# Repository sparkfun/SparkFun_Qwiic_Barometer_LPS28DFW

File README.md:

# SparkFun_Qwiic_Barometer_LPS28DFW

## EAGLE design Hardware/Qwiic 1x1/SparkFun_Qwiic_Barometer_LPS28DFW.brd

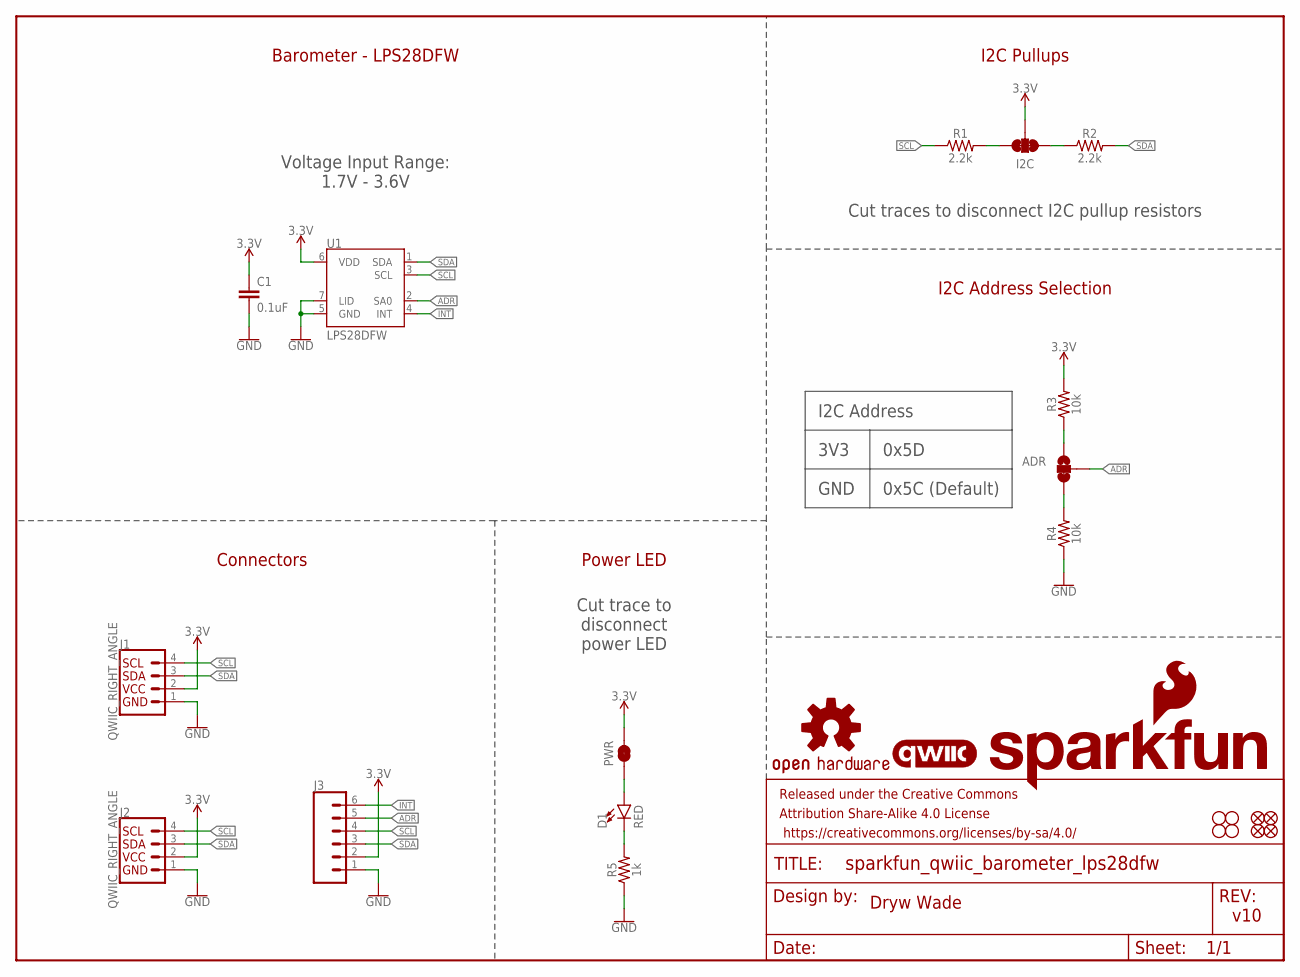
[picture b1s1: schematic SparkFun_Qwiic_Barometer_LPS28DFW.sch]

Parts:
ADR: JUMPER-SMT_3_1-NC_TRACE_SILK; SMT-JUMPER_3_1-NC_TRACE_SILK
C1: 0.1uF; 0603
D1: RED; LED-0603
FD1, FD2, FD3, FD4: FIDUCIAL1X2; FIDUCIAL-1X2
FRAME1: FRAME-LETTER; CREATIVE_COMMONS
H1, H2, H3, H4: STAND-OFF
I2C: JUMPER-SMT_3_2-NC_TRACE_SILK; SMT-JUMPER_3_2-NC_TRACE_SILK
J1, J2: QWIIC_RIGHT_ANGLE; JST04_1MM_RA
J3: CONN_06NO_SILK_NO_POP; 1X06_NO_SILK
LOGO1: OSHW-LOGOS; OSHW-LOGO-S
LOGO2: QWIIC_LOGO_5MM; QWIIC_5MM
LOGO3: SFE_LOGO_NAME_FLAME.1_INCH; SFE_LOGO_NAME_FLAME_.1
PWR: JUMPER-SMT_2_NC_TRACE_SILK; SMT-JUMPER_2_NC_TRACE_SILK
R1, R2: 2.2k; 0603
R3, R4: 10k; 0603
R5: 1k; 0603
U1: LPS28DFW

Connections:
3.3V: C1.1, I2C.2, J1.2, J2.2, J3.2, PWR.2, R3.2, U1.6 (VDD)
ADR: ADR.2, J3.5, U1.2 (SA0)
GND: C1.2, J1.1, J2.1, J3.1, R4.1, R5.1, U1.5 (GND), U1.7 (LID)
INT: J3.6, U1.4 (INT)
unnamed: D1.C, R5.2
unnamed: I2C.3, R1.2
unnamed: I2C.1, R2.1
unnamed: D1.A, PWR.1
unnamed: ADR.3, R4.2
unnamed: ADR.1, R3.1
SCL: J1.4, J2.4, J3.4, R1.1, U1.3 (SCL)
SDA: J1.3, J2.3, J3.3, R2.2, U1.1 (SDA)

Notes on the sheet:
Dryw Wade
v10
Barometer - LPS28DFW
I2C Pullups
I2C Address Selection
Connectors
Power LED
Cut traces to disconnect I2C pullup resistors
I2C Address
GND
3V3
0x5D
0x5C (Default)
Cut trace to disconnect power LED
Voltage Input Range: 1.7V - 3.6V

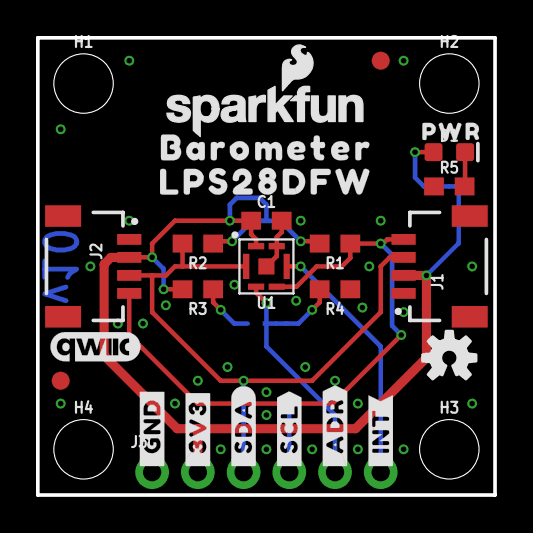
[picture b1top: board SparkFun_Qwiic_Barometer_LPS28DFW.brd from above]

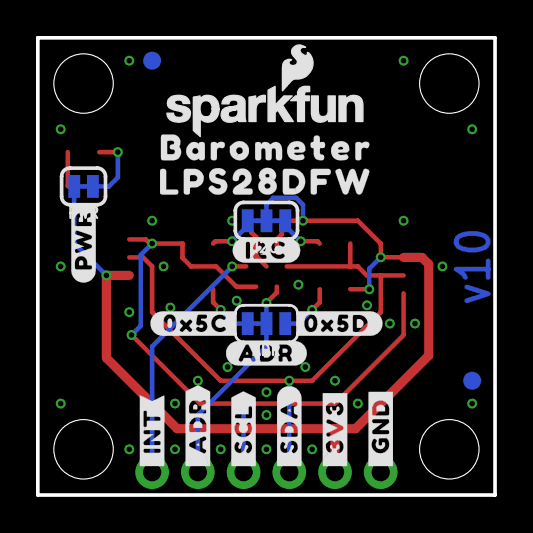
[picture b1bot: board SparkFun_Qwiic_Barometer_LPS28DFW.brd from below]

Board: 2 copper layers, 25.4 x 25.4 mm, 50 parts (19 on the bottom side), 12 nets.

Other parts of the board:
LOGO4: SFE_LOGO_NAME_FLAME.1_INCH; SFE_LOGO_NAME_FLAME_.1
U$1, U$2: #_GND#0
U$3, U$4: #_3V3#0
U$5, U$6: #_SDA#0
U$7, U$8: #_SCL#0
U$9: #I2C#0
U$10: #ADR#0
U$11, U$14: BAROMETER0
U$12, U$15: LPS28DFW0
U$13: #PWR#0
U$16: #0X5D#0
U$17: #0X5C#0
U$18: PWR0
U$19: ORDERING_INSTRUCTIONS
U$20, U$21: #_INT#0
U$22, U$23: #_ADR#0

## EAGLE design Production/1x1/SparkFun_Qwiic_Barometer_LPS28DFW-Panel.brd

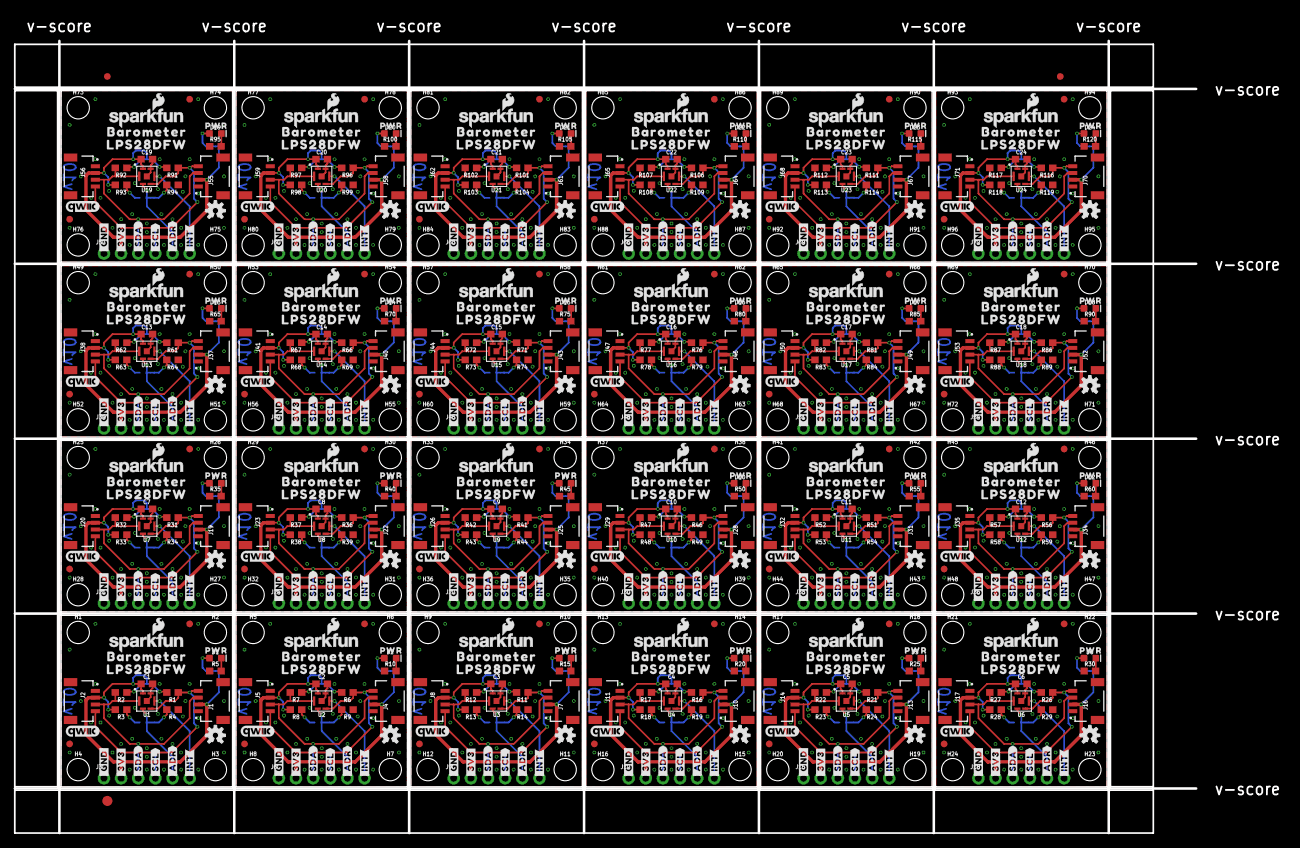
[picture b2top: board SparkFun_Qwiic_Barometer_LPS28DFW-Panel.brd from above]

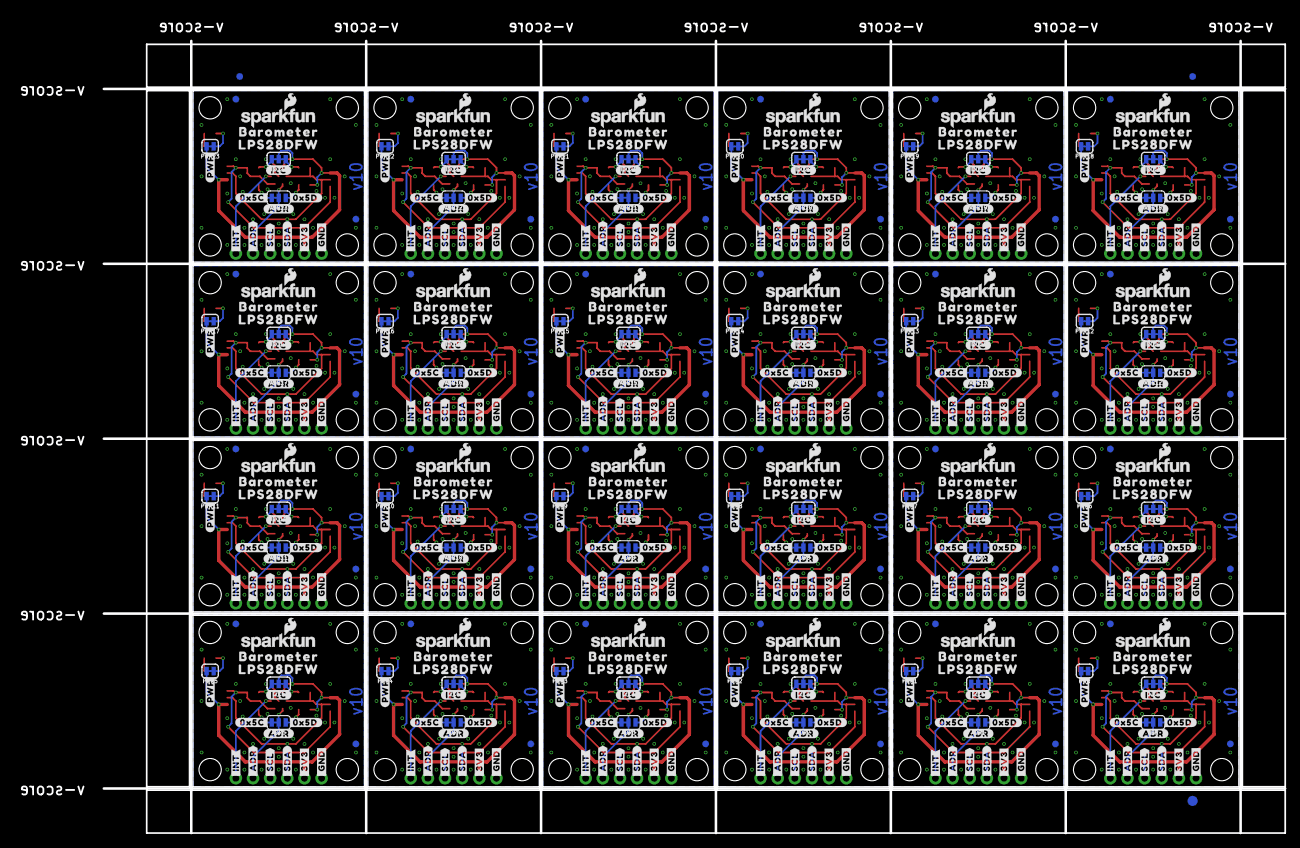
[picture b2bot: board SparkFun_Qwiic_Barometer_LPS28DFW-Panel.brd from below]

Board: 2 copper layers, 188.2 x 121.2 mm, 1158 parts (459 on the bottom side), 288 nets.

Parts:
ADR, ADR1, ADR2, ADR3, ADR4, ADR5, ADR6, ADR7, ADR8, ADR9, ADR10, ADR11, ADR12, ADR13, ADR14, ADR15, ADR16, ADR17, ADR18, ADR19, ADR20, ADR21, ADR22, ADR23: JUMPER-SMT_3_1-NC_TRACE_SILK; SMT-JUMPER_3_1-NC_TRACE_SILK
C1, C2, C3, C4, C5, C6, C7, C8, C9, C10, C11, C12, C13, C14, C15, C16, C17, C18, C19, C20, C21, C22, C23, C24: 0.1uF; 0603
D1, D2, D3, D4, D5, D6, D7, D8, D9, D10, D11, D12, D13, D14, D15, D16, D17, D18, D19, D20, D21, D22, D23, D24: RED; LED-0603
E$1, E$2, E$3, E$4: FIDUCIAL-1X2
E$5, E$6: FIDUCIAL-1.5X3
FD1, FD2, FD3, FD4, FD5, FD6, FD7, FD8, FD9, FD10, FD11, FD12, FD13, FD14, FD15, FD16, FD17, FD18, FD19, FD20, FD21, FD22, FD23, FD24, FD25, FD26, FD27, FD28, FD29, FD30, FD31, FD32, FD33, FD34, FD35, FD36, FD37, FD38, FD39, FD40, FD41, FD42, FD43, FD44, FD45, FD46, FD47, FD48, FD49, FD50, FD51, FD52, FD53, FD54, FD55, FD56, FD57, FD58, FD59, FD60, FD61, FD62, FD63, FD64, FD65, FD66, FD67, FD68, FD69, FD70, FD71, FD72, FD73, FD74, FD75, FD76, FD77, FD78, FD79, FD80, FD81, FD82, FD83, FD84, FD85, FD86, FD87, FD88, FD89, FD90, FD91, FD92, FD93, FD94, FD95, FD96: FIDUCIAL1X2; FIDUCIAL-1X2
H1, H2, H3, H4, H5, H6, H7, H8, H9, H10, H11, H12, H13, H14, H15, H16, H17, H18, H19, H20, H21, H22, H23, H24, H25, H26, H27, H28, H29, H30, H31, H32, H33, H34, H35, H36, H37, H38, H39, H40, H41, H42, H43, H44, H45, H46, H47, H48, H49, H50, H51, H52, H53, H54, H55, H56, H57, H58, H59, H60, H61, H62, H63, H64, H65, H66, H67, H68, H69, H70, H71, H72, H73, H74, H75, H76, H77, H78, H79, H80, H81, H82, H83, H84, H85, H86, H87, H88, H89, H90, H91, H92, H93, H94, H95, H96: STAND-OFF
I2C, I2C1, I2C2, I2C3, I2C4, I2C5, I2C6, I2C7, I2C8, I2C9, I2C10, I2C11, I2C12, I2C13, I2C14, I2C15, I2C16, I2C17, I2C18, I2C19, I2C20, I2C21, I2C22, I2C23: JUMPER-SMT_3_2-NC_TRACE_SILK; SMT-JUMPER_3_2-NC_TRACE_SILK
J1, J2, J4, J5, J7, J8, J10, J11, J13, J14, J16, J17, J19, J20, J22, J23, J25, J26, J28, J29, J31, J32, J34, J35, J37, J38, J40, J41, J43, J44, J46, J47, J49, J50, J52, J53, J55, J56, J58, J59, J61, J62, J64, J65, J67, J68, J70, J71: QWIIC_RIGHT_ANGLE; JST04_1MM_RA
J3, J6, J9, J12, J15, J18, J21, J24, J27, J30, J33, J36, J39, J42, J45, J48, J51, J54, J57, J60, J63, J66, J69, J72: 1X06_NO_SILK
LOGO1, LOGO5, LOGO9, LOGO13, LOGO17, LOGO21, LOGO25, LOGO29, LOGO33, LOGO37, LOGO41, LOGO45, LOGO49, LOGO53, LOGO57, LOGO61, LOGO65, LOGO69, LOGO73, LOGO77, LOGO81, LOGO85, LOGO89, LOGO93: OSHW-LOGOS; OSHW-LOGO-S
LOGO2, LOGO6, LOGO10, LOGO14, LOGO18, LOGO22, LOGO26, LOGO30, LOGO34, LOGO38, LOGO42, LOGO46, LOGO50, LOGO54, LOGO58, LOGO62, LOGO66, LOGO70, LOGO74, LOGO78, LOGO82, LOGO86, LOGO90, LOGO94: QWIIC_LOGO_5MM; QWIIC_5MM
LOGO3, LOGO4, LOGO7, LOGO8, LOGO11, LOGO12, LOGO15, LOGO16, LOGO19, LOGO20, LOGO23, LOGO24, LOGO27, LOGO28, LOGO31, LOGO32, LOGO35, LOGO36, LOGO39, LOGO40, LOGO43, LOGO44, LOGO47, LOGO48, LOGO51, LOGO52, LOGO55, LOGO56, LOGO59, LOGO60, LOGO63, LOGO64, LOGO67, LOGO68, LOGO71, LOGO72, LOGO75, LOGO76, LOGO79, LOGO80, LOGO83, LOGO84, LOGO87, LOGO88, LOGO91, LOGO92, LOGO95, LOGO96: SFE_LOGO_NAME_FLAME.1_INCH; SFE_LOGO_NAME_FLAME_.1
PWR, PWR1, PWR2, PWR3, PWR4, PWR5, PWR6, PWR7, PWR8, PWR9, PWR10, PWR11, PWR12, PWR13, PWR14, PWR15, PWR16, PWR17, PWR18, PWR19, PWR20, PWR21, PWR22, PWR23: JUMPER-SMT_2_NC_TRACE_SILK; SMT-JUMPER_2_NC_TRACE_SILK
R1, R2, R6, R7, R11, R12, R16, R17, R21, R22, R26, R27, R31, R32, R36, R37, R41, R42, R46, R47, R51, R52, R56, R57, R61, R62, R66, R67, R71, R72, R76, R77, R81, R82, R86, R87, R91, R92, R96, R97, R101, R102, R106, R107, R111, R112, R116, R117: 2.2k; 0603
R3, R4, R8, R9, R13, R14, R18, R19, R23, R24, R28, R29, R33, R34, R38, R39, R43, R44, R48, R49, R53, R54, R58, R59, R63, R64, R68, R69, R73, R74, R78, R79, R83, R84, R88, R89, R93, R94, R98, R99, R103, R104, R108, R109, R113, R114, R118, R119: 10k; 0603
R5, R10, R15, R20, R25, R30, R35, R40, R45, R50, R55, R60, R65, R70, R75, R80, R85, R90, R95, R100, R105, R110, R115, R120: 1k; 0603
U1, U2, U3, U4, U5, U6, U7, U8, U9, U10, U11, U12, U13, U14, U15, U16, U17, U18, U19, U20, U21, U22, U23, U24: LPS28DFW
U$1, U$2, U$19, U$24, U$45, U$46, U$67, U$68, U$89, U$90, U$111, U$112, U$133, U$134, U$155, U$156, U$177, U$178, U$199, U$200, U$221, U$222, U$243, U$244, U$265, U$266, U$287, U$288, U$309, U$310, U$331, U$332, U$353, U$354, U$375, U$376, U$397, U$398, U$419, U$420, U$441, U$442, U$463, U$464, U$485, U$486, U$507, U$508: #_GND#0
U$3, U$4, U$25, U$26, U$47, U$48, U$69, U$70, U$91, U$92, U$113, U$114, U$135, U$136, U$157, U$158, U$179, U$180, U$201, U$202, U$223, U$224, U$245, U$246, U$267, U$268, U$289, U$290, U$311, U$312, U$333, U$334, U$355, U$356, U$377, U$378, U$399, U$400, U$421, U$422, U$443, U$444, U$465, U$466, U$487, U$488, U$509, U$510: #_3V3#0
U$5, U$6, U$27, U$28, U$49, U$50, U$71, U$72, U$93, U$94, U$115, U$116, U$137, U$138, U$159, U$160, U$181, U$182, U$203, U$204, U$225, U$226, U$247, U$248, U$269, U$270, U$291, U$292, U$313, U$314, U$335, U$336, U$357, U$358, U$379, U$380, U$401, U$402, U$423, U$424, U$445, U$446, U$467, U$468, U$489, U$490, U$511, U$512: #_SDA#0
U$7, U$8, U$29, U$30, U$51, U$52, U$73, U$74, U$95, U$96, U$117, U$118, U$139, U$140, U$161, U$162, U$183, U$184, U$205, U$206, U$227, U$228, U$249, U$250, U$271, U$272, U$293, U$294, U$315, U$316, U$337, U$338, U$359, U$360, U$381, U$382, U$403, U$404, U$425, U$426, U$447, U$448, U$469, U$470, U$491, U$492, U$513, U$514: #_SCL#0
U$9, U$31, U$53, U$75, U$97, U$119, U$141, U$163, U$185, U$207, U$229, U$251, U$273, U$295, U$317, U$339, U$361, U$383, U$405, U$427, U$449, U$471, U$493, U$515: #I2C#0
U$10, U$32, U$54, U$76, U$98, U$120, U$142, U$164, U$186, U$208, U$230, U$252, U$274, U$296, U$318, U$340, U$362, U$384, U$406, U$428, U$450, U$472, U$494, U$516: #ADR#0
U$11, U$14, U$33, U$36, U$55, U$58, U$77, U$80, U$99, U$102, U$121, U$124, U$143, U$146, U$165, U$168, U$187, U$190, U$209, U$212, U$231, U$234, U$253, U$256, U$275, U$278, U$297, U$300, U$319, U$322, U$341, U$344, U$363, U$366, U$385, U$388, U$407, U$410, U$429, U$432, U$451, U$454, U$473, U$476, U$495, U$498, U$517, U$520: BAROMETER0
U$12, U$15, U$34, U$37, U$56, U$59, U$78, U$81, U$100, U$103, U$122, U$125, U$144, U$147, U$166, U$169, U$188, U$191, U$210, U$213, U$232, U$235, U$254, U$257, U$276, U$279, U$298, U$301, U$320, U$323, U$342, U$345, U$364, U$367, U$386, U$389, U$408, U$411, U$430, U$433, U$452, U$455, U$474, U$477, U$496, U$499, U$518, U$521: LPS28DFW0
U$13, U$35, U$57, U$79, U$101, U$123, U$145, U$167, U$189, U$211, U$233, U$255, U$277, U$299, U$321, U$343, U$365, U$387, U$409, U$431, U$453, U$475, U$497, U$519: #PWR#0
U$16, U$38, U$60, U$82, U$104, U$126, U$148, U$170, U$192, U$214, U$236, U$258, U$280, U$302, U$324, U$346, U$368, U$390, U$412, U$434, U$456, U$478, U$500, U$522: #0X5D#0
U$17, U$39, U$61, U$83, U$105, U$127, U$149, U$171, U$193, U$215, U$237, U$259, U$281, U$303, U$325, U$347, U$369, U$391, U$413, U$435, U$457, U$479, U$501, U$523: #0X5C#0
U$18, U$44, U$66, U$88, U$110, U$132, U$154, U$176, U$198, U$220, U$242, U$264, U$286, U$308, U$330, U$352, U$374, U$396, U$418, U$440, U$462, U$484, U$506, U$528: PWR0
U$20, U$21, U$40, U$41, U$62, U$63, U$84, U$85, U$106, U$107, U$128, U$129, U$150, U$151, U$172, U$173, U$194, U$195, U$216, U$217, U$238, U$239, U$260, U$261, U$282, U$283, U$304, U$305, U$326, U$327, U$348, U$349, U$370, U$371, U$392, U$393, U$414, U$415, U$436, U$437, U$458, U$459, U$480, U$481, U$502, U$503, U$524, U$525: #_INT#0
U$22, U$23, U$42, U$43, U$64, U$65, U$86, U$87, U$108, U$109, U$130, U$131, U$152, U$153, U$174, U$175, U$196, U$197, U$218, U$219, U$240, U$241, U$262, U$263, U$284, U$285, U$306, U$307, U$328, U$329, U$350, U$351, U$372, U$373, U$394, U$395, U$416, U$417, U$438, U$439, U$460, U$461, U$482, U$483, U$504, U$505, U$526, U$527: #_ADR#0

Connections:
3.3V: C1.1, I2C.2, J1.2, J2.2, J3.2, PWR.2, R3.2, U1.6
3.3V1: C2.1, I2C1.2, J4.2, J5.2, J6.2, PWR1.2, R8.2, U2.6
3.3V2: C3.1, I2C2.2, J7.2, J8.2, J9.2, PWR2.2, R13.2, U3.6
3.3V3: C4.1, I2C3.2, J10.2, J11.2, J12.2, PWR3.2, R18.2, U4.6
3.3V4: C5.1, I2C4.2, J13.2, J14.2, J15.2, PWR4.2, R23.2, U5.6
3.3V5: C6.1, I2C5.2, J16.2, J17.2, J18.2, PWR5.2, R28.2, U6.6
3.3V6: C7.1, I2C6.2, J19.2, J20.2, J21.2, PWR6.2, R33.2, U7.6
3.3V7: C8.1, I2C7.2, J22.2, J23.2, J24.2, PWR7.2, R38.2, U8.6
3.3V8: C9.1, I2C8.2, J25.2, J26.2, J27.2, PWR8.2, R43.2, U9.6
3.3V9: C10.1, I2C9.2, J28.2, J29.2, J30.2, PWR9.2, R48.2, U10.6
3.3V10: C11.1, I2C10.2, J31.2, J32.2, J33.2, PWR10.2, R53.2, U11.6
3.3V11: C12.1, I2C11.2, J34.2, J35.2, J36.2, PWR11.2, R58.2, U12.6
3.3V12: C13.1, I2C12.2, J37.2, J38.2, J39.2, PWR12.2, R63.2, U13.6
3.3V13: C14.1, I2C13.2, J40.2, J41.2, J42.2, PWR13.2, R68.2, U14.6
3.3V14: C15.1, I2C14.2, J43.2, J44.2, J45.2, PWR14.2, R73.2, U15.6
3.3V15: C16.1, I2C15.2, J46.2, J47.2, J48.2, PWR15.2, R78.2, U16.6
3.3V16: C17.1, I2C16.2, J49.2, J50.2, J51.2, PWR16.2, R83.2, U17.6
3.3V17: C18.1, I2C17.2, J52.2, J53.2, J54.2, PWR17.2, R88.2, U18.6
3.3V18: C19.1, I2C18.2, J55.2, J56.2, J57.2, PWR18.2, R93.2, U19.6
3.3V19: C20.1, I2C19.2, J58.2, J59.2, J60.2, PWR19.2, R98.2, U20.6
3.3V20: C21.1, I2C20.2, J61.2, J62.2, J63.2, PWR20.2, R103.2, U21.6
3.3V21: C22.1, I2C21.2, J64.2, J65.2, J66.2, PWR21.2, R108.2, U22.6
3.3V22: C23.1, I2C22.2, J67.2, J68.2, J69.2, PWR22.2, R113.2, U23.6
3.3V23: C24.1, I2C23.2, J70.2, J71.2, J72.2, PWR23.2, R118.2, U24.6
ADR: ADR.2, J3.5, U1.2
ADR1: ADR1.2, J6.5, U2.2
ADR2: ADR2.2, J9.5, U3.2
ADR3: ADR3.2, J12.5, U4.2
ADR4: ADR4.2, J15.5, U5.2
ADR5: ADR5.2, J18.5, U6.2
ADR6: ADR6.2, J21.5, U7.2
ADR7: ADR7.2, J24.5, U8.2
ADR8: ADR8.2, J27.5, U9.2
ADR9: ADR9.2, J30.5, U10.2
ADR10: ADR10.2, J33.5, U11.2
ADR11: ADR11.2, J36.5, U12.2
ADR12: ADR12.2, J39.5, U13.2
ADR13: ADR13.2, J42.5, U14.2
ADR14: ADR14.2, J45.5, U15.2
ADR15: ADR15.2, J48.5, U16.2
ADR16: ADR16.2, J51.5, U17.2
ADR17: ADR17.2, J54.5, U18.2
ADR18: ADR18.2, J57.5, U19.2
ADR19: ADR19.2, J60.5, U20.2
ADR20: ADR20.2, J63.5, U21.2
ADR21: ADR21.2, J66.5, U22.2
ADR22: ADR22.2, J69.5, U23.2
ADR23: ADR23.2, J72.5, U24.2
GND: C1.2, J1.1, J2.1, J3.1, R4.1, R5.1, U1.5, U1.7
GND1: C2.2, J4.1, J5.1, J6.1, R9.1, R10.1, U2.5, U2.7
GND2: C3.2, J7.1, J8.1, J9.1, R14.1, R15.1, U3.5, U3.7
GND3: C4.2, J10.1, J11.1, J12.1, R19.1, R20.1, U4.5, U4.7
GND4: C5.2, J13.1, J14.1, J15.1, R24.1, R25.1, U5.5, U5.7
GND5: C6.2, J16.1, J17.1, J18.1, R29.1, R30.1, U6.5, U6.7
GND6: C7.2, J19.1, J20.1, J21.1, R34.1, R35.1, U7.5, U7.7
GND7: C8.2, J22.1, J23.1, J24.1, R39.1, R40.1, U8.5, U8.7
GND8: C9.2, J25.1, J26.1, J27.1, R44.1, R45.1, U9.5, U9.7
GND9: C10.2, J28.1, J29.1, J30.1, R49.1, R50.1, U10.5, U10.7
GND10: C11.2, J31.1, J32.1, J33.1, R54.1, R55.1, U11.5, U11.7
GND11: C12.2, J34.1, J35.1, J36.1, R59.1, R60.1, U12.5, U12.7
GND12: C13.2, J37.1, J38.1, J39.1, R64.1, R65.1, U13.5, U13.7
GND13: C14.2, J40.1, J41.1, J42.1, R69.1, R70.1, U14.5, U14.7
GND14: C15.2, J43.1, J44.1, J45.1, R74.1, R75.1, U15.5, U15.7
GND15: C16.2, J46.1, J47.1, J48.1, R79.1, R80.1, U16.5, U16.7
GND16: C17.2, J49.1, J50.1, J51.1, R84.1, R85.1, U17.5, U17.7
GND17: C18.2, J52.1, J53.1, J54.1, R89.1, R90.1, U18.5, U18.7
GND18: C19.2, J55.1, J56.1, J57.1, R94.1, R95.1, U19.5, U19.7
GND19: C20.2, J58.1, J59.1, J60.1, R99.1, R100.1, U20.5, U20.7
GND20: C21.2, J61.1, J62.1, J63.1, R104.1, R105.1, U21.5, U21.7
GND21: C22.2, J64.1, J65.1, J66.1, R109.1, R110.1, U22.5, U22.7
GND22: C23.2, J67.1, J68.1, J69.1, R114.1, R115.1, U23.5, U23.7
GND23: C24.2, J70.1, J71.1, J72.1, R119.1, R120.1, U24.5, U24.7
INT: J3.6, U1.4
INT1: J6.6, U2.4
INT2: J9.6, U3.4
INT3: J12.6, U4.4
INT4: J15.6, U5.4
INT5: J18.6, U6.4
INT6: J21.6, U7.4
INT7: J24.6, U8.4
INT8: J27.6, U9.4
INT9: J30.6, U10.4
INT10: J33.6, U11.4
INT11: J36.6, U12.4
INT12: J39.6, U13.4
INT13: J42.6, U14.4
INT14: J45.6, U15.4
INT15: J48.6, U16.4
INT16: J51.6, U17.4
INT17: J54.6, U18.4
INT18: J57.6, U19.4
INT19: J60.6, U20.4
INT20: J63.6, U21.4
INT21: J66.6, U22.4
INT22: J69.6, U23.4
INT23: J72.6, U24.4
unnamed: D1.C, R5.2
unnamed: I2C.3, R1.2
unnamed: I2C.1, R2.1
unnamed: D1.A, PWR.1
unnamed: ADR.3, R4.2
unnamed: ADR.1, R3.1
unnamed: I2C1.3, R6.2
unnamed: I2C1.1, R7.1
unnamed: ADR1.3, R9.2
unnamed: ADR1.1, R8.1
unnamed: D2.C, R10.2
unnamed: D2.A, PWR1.1
unnamed: I2C2.3, R11.2
unnamed: I2C2.1, R12.1
unnamed: ADR2.3, R14.2
unnamed: ADR2.1, R13.1
unnamed: D3.C, R15.2
unnamed: D3.A, PWR2.1
unnamed: I2C3.3, R16.2
unnamed: I2C3.1, R17.1
unnamed: ADR3.3, R19.2
unnamed: ADR3.1, R18.1
unnamed: D4.C, R20.2
unnamed: D4.A, PWR3.1
unnamed: I2C4.3, R21.2
unnamed: I2C4.1, R22.1
unnamed: ADR4.3, R24.2
unnamed: ADR4.1, R23.1
unnamed: D5.C, R25.2
unnamed: D5.A, PWR4.1
unnamed: I2C5.3, R26.2
unnamed: I2C5.1, R27.1
unnamed: ADR5.3, R29.2
unnamed: ADR5.1, R28.1
unnamed: D6.C, R30.2
unnamed: D6.A, PWR5.1
unnamed: I2C6.3, R31.2
unnamed: I2C6.1, R32.1
unnamed: ADR6.3, R34.2
unnamed: ADR6.1, R33.1
unnamed: D7.C, R35.2
unnamed: D7.A, PWR6.1
unnamed: I2C7.3, R36.2
unnamed: I2C7.1, R37.1
unnamed: ADR7.3, R39.2
unnamed: ADR7.1, R38.1
unnamed: D8.C, R40.2
unnamed: D8.A, PWR7.1
unnamed: I2C8.3, R41.2
unnamed: I2C8.1, R42.1
unnamed: ADR8.3, R44.2
unnamed: ADR8.1, R43.1
unnamed: D9.C, R45.2
unnamed: D9.A, PWR8.1
unnamed: I2C9.3, R46.2
unnamed: I2C9.1, R47.1
unnamed: ADR9.3, R49.2
unnamed: ADR9.1, R48.1
unnamed: D10.C, R50.2
unnamed: D10.A, PWR9.1
unnamed: I2C10.3, R51.2
unnamed: I2C10.1, R52.1
unnamed: ADR10.3, R54.2
unnamed: ADR10.1, R53.1
unnamed: D11.C, R55.2
unnamed: D11.A, PWR10.1
unnamed: I2C11.3, R56.2
unnamed: I2C11.1, R57.1
unnamed: ADR11.3, R59.2
unnamed: ADR11.1, R58.1
unnamed: D12.C, R60.2
unnamed: D12.A, PWR11.1
unnamed: I2C12.3, R61.2
unnamed: I2C12.1, R62.1
unnamed: ADR12.3, R64.2
unnamed: ADR12.1, R63.1
unnamed: D13.C, R65.2
unnamed: D13.A, PWR12.1
unnamed: I2C13.3, R66.2
unnamed: I2C13.1, R67.1
unnamed: ADR13.3, R69.2
unnamed: ADR13.1, R68.1
unnamed: D14.C, R70.2
unnamed: D14.A, PWR13.1
unnamed: I2C14.3, R71.2
unnamed: I2C14.1, R72.1
unnamed: ADR14.3, R74.2
unnamed: ADR14.1, R73.1
unnamed: D15.C, R75.2
unnamed: D15.A, PWR14.1
unnamed: I2C15.3, R76.2
unnamed: I2C15.1, R77.1
unnamed: ADR15.3, R79.2
unnamed: ADR15.1, R78.1
unnamed: D16.C, R80.2
unnamed: D16.A, PWR15.1
unnamed: I2C16.3, R81.2
unnamed: I2C16.1, R82.1
unnamed: ADR16.3, R84.2
unnamed: ADR16.1, R83.1
unnamed: D17.C, R85.2
unnamed: D17.A, PWR16.1
unnamed: I2C17.3, R86.2
unnamed: I2C17.1, R87.1
unnamed: ADR17.3, R89.2
unnamed: ADR17.1, R88.1
unnamed: D18.C, R90.2
unnamed: D18.A, PWR17.1
unnamed: I2C18.3, R91.2
unnamed: I2C18.1, R92.1
unnamed: ADR18.3, R94.2
unnamed: ADR18.1, R93.1
unnamed: D19.C, R95.2
unnamed: D19.A, PWR18.1
unnamed: I2C19.3, R96.2
unnamed: I2C19.1, R97.1
unnamed: ADR19.3, R99.2
unnamed: ADR19.1, R98.1
unnamed: D20.C, R100.2
unnamed: D20.A, PWR19.1
unnamed: I2C20.3, R101.2
unnamed: I2C20.1, R102.1
unnamed: ADR20.3, R104.2
unnamed: ADR20.1, R103.1
unnamed: D21.C, R105.2
unnamed: D21.A, PWR20.1
unnamed: I2C21.3, R106.2
unnamed: I2C21.1, R107.1
unnamed: ADR21.3, R109.2
unnamed: ADR21.1, R108.1
unnamed: D22.C, R110.2
unnamed: D22.A, PWR21.1
unnamed: I2C22.3, R111.2
unnamed: I2C22.1, R112.1
unnamed: ADR22.3, R114.2
unnamed: ADR22.1, R113.1
unnamed: D23.C, R115.2
unnamed: D23.A, PWR22.1
unnamed: I2C23.3, R116.2
unnamed: I2C23.1, R117.1
unnamed: ADR23.3, R119.2
unnamed: ADR23.1, R118.1
unnamed: D24.C, R120.2
unnamed: D24.A, PWR23.1
SCL: J1.4, J2.4, J3.4, R1.1, U1.3
SCL1: J4.4, J5.4, J6.4, R6.1, U2.3
SCL2: J7.4, J8.4, J9.4, R11.1, U3.3
SCL3: J10.4, J11.4, J12.4, R16.1, U4.3
SCL4: J13.4, J14.4, J15.4, R21.1, U5.3
SCL5: J16.4, J17.4, J18.4, R26.1, U6.3
SCL6: J19.4, J20.4, J21.4, R31.1, U7.3
SCL7: J22.4, J23.4, J24.4, R36.1, U8.3
SCL8: J25.4, J26.4, J27.4, R41.1, U9.3
SCL9: J28.4, J29.4, J30.4, R46.1, U10.3
SCL10: J31.4, J32.4, J33.4, R51.1, U11.3
SCL11: J34.4, J35.4, J36.4, R56.1, U12.3
SCL12: J37.4, J38.4, J39.4, R61.1, U13.3
SCL13: J40.4, J41.4, J42.4, R66.1, U14.3
SCL14: J43.4, J44.4, J45.4, R71.1, U15.3
SCL15: J46.4, J47.4, J48.4, R76.1, U16.3
SCL16: J49.4, J50.4, J51.4, R81.1, U17.3
SCL17: J52.4, J53.4, J54.4, R86.1, U18.3
SCL18: J55.4, J56.4, J57.4, R91.1, U19.3
SCL19: J58.4, J59.4, J60.4, R96.1, U20.3
SCL20: J61.4, J62.4, J63.4, R101.1, U21.3
SCL21: J64.4, J65.4, J66.4, R106.1, U22.3
SCL22: J67.4, J68.4, J69.4, R111.1, U23.3
SCL23: J70.4, J71.4, J72.4, R116.1, U24.3
SDA: J1.3, J2.3, J3.3, R2.2, U1.1
SDA1: J4.3, J5.3, J6.3, R7.2, U2.1
SDA2: J7.3, J8.3, J9.3, R12.2, U3.1
SDA3: J10.3, J11.3, J12.3, R17.2, U4.1
SDA4: J13.3, J14.3, J15.3, R22.2, U5.1
SDA5: J16.3, J17.3, J18.3, R27.2, U6.1
SDA6: J19.3, J20.3, J21.3, R32.2, U7.1
SDA7: J22.3, J23.3, J24.3, R37.2, U8.1
SDA8: J25.3, J26.3, J27.3, R42.2, U9.1
SDA9: J28.3, J29.3, J30.3, R47.2, U10.1
SDA10: J31.3, J32.3, J33.3, R52.2, U11.1
SDA11: J34.3, J35.3, J36.3, R57.2, U12.1
SDA12: J37.3, J38.3, J39.3, R62.2, U13.1
SDA13: J40.3, J41.3, J42.3, R67.2, U14.1
SDA14: J43.3, J44.3, J45.3, R72.2, U15.1
SDA15: J46.3, J47.3, J48.3, R77.2, U16.1
SDA16: J49.3, J50.3, J51.3, R82.2, U17.1
SDA17: J52.3, J53.3, J54.3, R87.2, U18.1
SDA18: J55.3, J56.3, J57.3, R92.2, U19.1
SDA19: J58.3, J59.3, J60.3, R97.2, U20.1
SDA20: J61.3, J62.3, J63.3, R102.2, U21.1
SDA21: J64.3, J65.3, J66.3, R107.2, U22.1
SDA22: J67.3, J68.3, J69.3, R112.2, U23.1
SDA23: J70.3, J71.3, J72.3, R117.2, U24.1

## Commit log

2022-09-19 Add datasheet
2022-09-19 Create LPS28DFW library file
2022-09-19 Create initial schematic and board layout
2022-09-19 Add initial Qwiic Micro schematic and board layout
2022-09-19 Mirror LPS28DFW
    Turns out the bottom view is not the same as the top view...
    Also add tKeepout
2022-09-19 Update 1x1 with mirrored LPS28DFW footprint
2022-09-19 Update Micro with mirrored LPS28DFW footprint
2022-09-20 Design review updates
    Add silk to PWR LED on 1x1
    Tweak routing to use more T-junctions and route into side of pads rather than corners
    Move via on I2C jumper silk of Micro
2022-09-20 Move LPS28DFW pin 1 indicator silk
2022-09-26 Add PROD_ID to LPS28DFW
2022-10-20 Design review updates
    Both:
    Bump version number to v10
    Change LPS28DF section name to "Barometer - LPS28DFW" in schematics
    Remove SPI from ADR jumper in schematics
    Add ordering instructions to boards
    1x1:
2022-10-20 Move OSHW logo in 1x1
2022-10-20 Create v10 panels
2022-12-06 Update README.md
    Updating README.md for release.
2023-03-28 Remove library file
    Part is in SFE Eagle library, update part in design

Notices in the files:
parts and their libraries:
SparkFun-Aesthetics: Licensing: Creative Commons ShareAlike 4.0 International - https://creativecommons.org/licenses/by-sa/4.0
SparkFun-Aesthetics: Released under the Creative Commons Attribution Share-Alike 4.0 License
SparkFun-Aesthetics: https://creativecommons.org/licenses/by-sa/4.0
